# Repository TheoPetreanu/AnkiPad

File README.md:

# Theo’s Study Hackpad
This project was funded by a Blueprint (Hack Club) hardware grant, awarded following a design proposal and build journal review.

## Inspiration

I wanted to build a dedicated study-focused macropad to speed up my Anki revision and control YouTube without breaking focus. Instead of using keyboard shortcuts or mouse clicks, this hackpad allows for one handed control of my two most commonly used revision resources: Yotube and Anki.

## Challenges

One of the main challenges was designing a PCB that cleanly integrated mechanical switches, a rotary encoder, and addressable RGB LEDs while keeping the layout compact.

Another challenge was structuring the firmware cleanly using KMK, especially handling multiple modes (layers), encoder input, and an LED indicator

Designing the case to ensure proper alignment between the PCB, switches, encoder, and USB port also required several iterations.

## Specifications
### Modes:

Modes are switched by pressing the rotary encoder.

#### Anki Mode:

Blue LED indicator

Dedicated answer and control keys

#### YouTube Mode:

Red LED indicator

Playback and navigation controls

### BOM

1× XIAO RP2040

5× MX-style mechanical switches

5× Keycaps

1× EC11 Rotary encoder 

2× SK6812 MINI addressable RGB LEDs

Custom PCB

3D printed case (top + bottom)

USB Cable

### Firmware

KMK (CircuitPython-based firmware)

Two-layer setup (Anki / YouTube)

Encoder rotation for volume control

Encoder press for mode switching

RGB LEDs used as mode indicators

Firmware files are located in the firmware/ directory.

## Images
### Schematic

### PCB

### Case

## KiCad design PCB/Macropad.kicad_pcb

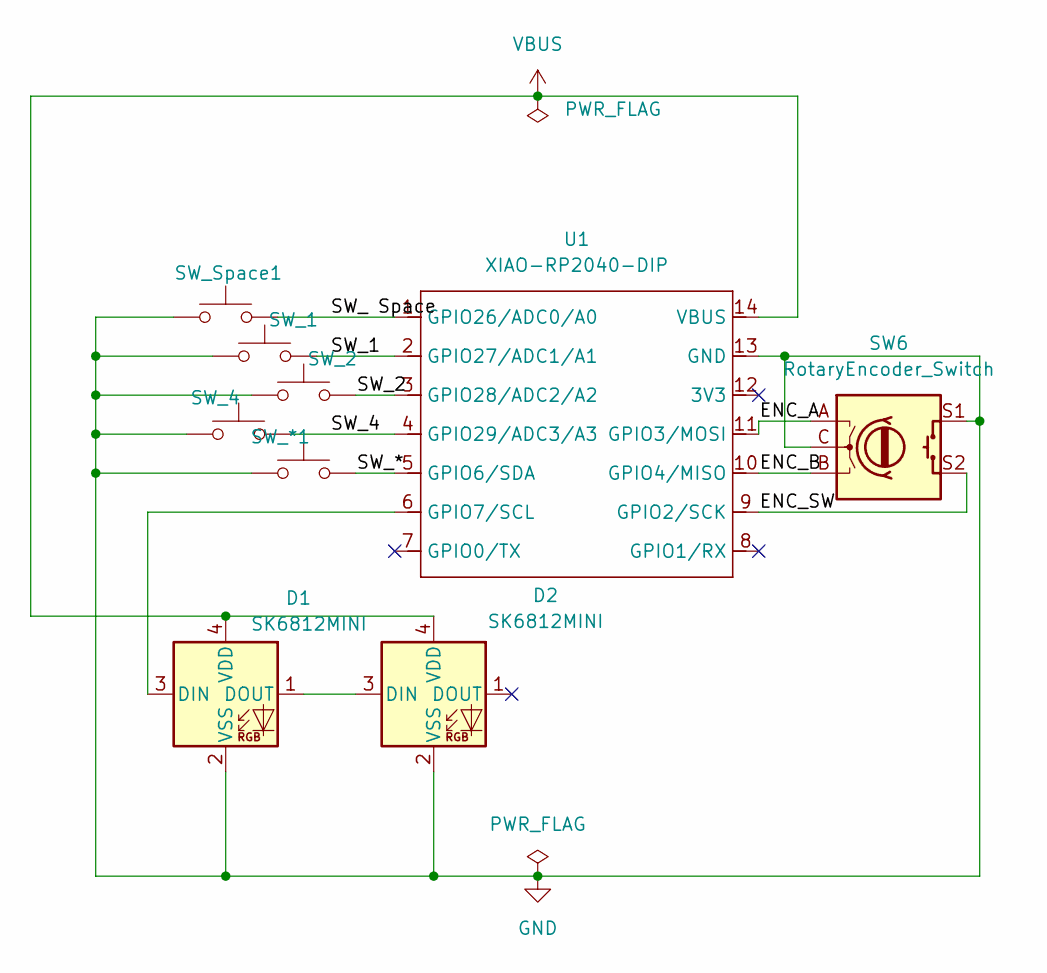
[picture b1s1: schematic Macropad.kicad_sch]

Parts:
D1, D2: SK6812MINI; LED_SK6812MINI_PLCC4_3.5x3.5mm_P1.75mm
SW6: RotaryEncoder_Switch; RotaryEncoder_Alps_EC11E-Switch_Vertical_H20mm
SW_1, SW_2, SW_4: SW_Push; SW_Cherry_MX_1.00u_PCB
SW_*1: SW_Push; SW_Cherry_MX_1.00u_PCB
SW_Space1: SW_Push; SW_Cherry_MX_1.00u_PCB
U1: XIAO-RP2040-DIP

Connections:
/ENC_A: SW6.A, U1.11 (GPIO3/MOSI)
/ENC_B: SW6.B, U1.10 (GPIO4/MISO)
/ENC_SW: SW6.S2, U1.9 (GPIO2/SCK)
/SW_1: SW_1.2, U1.2 (GPIO27/ADC1/A1)
/SW_2: SW_2.2, U1.3 (GPIO28/ADC2/A2)
/SW_4: SW_4.2, U1.4 (GPIO29/ADC3/A3)
/SW_ Space: SW_Space1.2, U1.1 (GPIO26/ADC0/A0)
/SW_*: SW_*1.2, U1.5 (GPIO6/SDA)
GND: D1.2 (VSS), D2.2 (VSS), SW6.C, SW6.S1, SW_1.1, SW_2.1, SW_4.1, SW_*1.1, SW_Space1.1, U1.13 (GND)
unnamed: D1.3 (DIN), U1.6 (GPIO7/SCL)
unnamed: D1.1 (DOUT), D2.3 (DIN)
VBUS: D1.4 (VDD), D2.4 (VDD), U1.14 (VBUS)

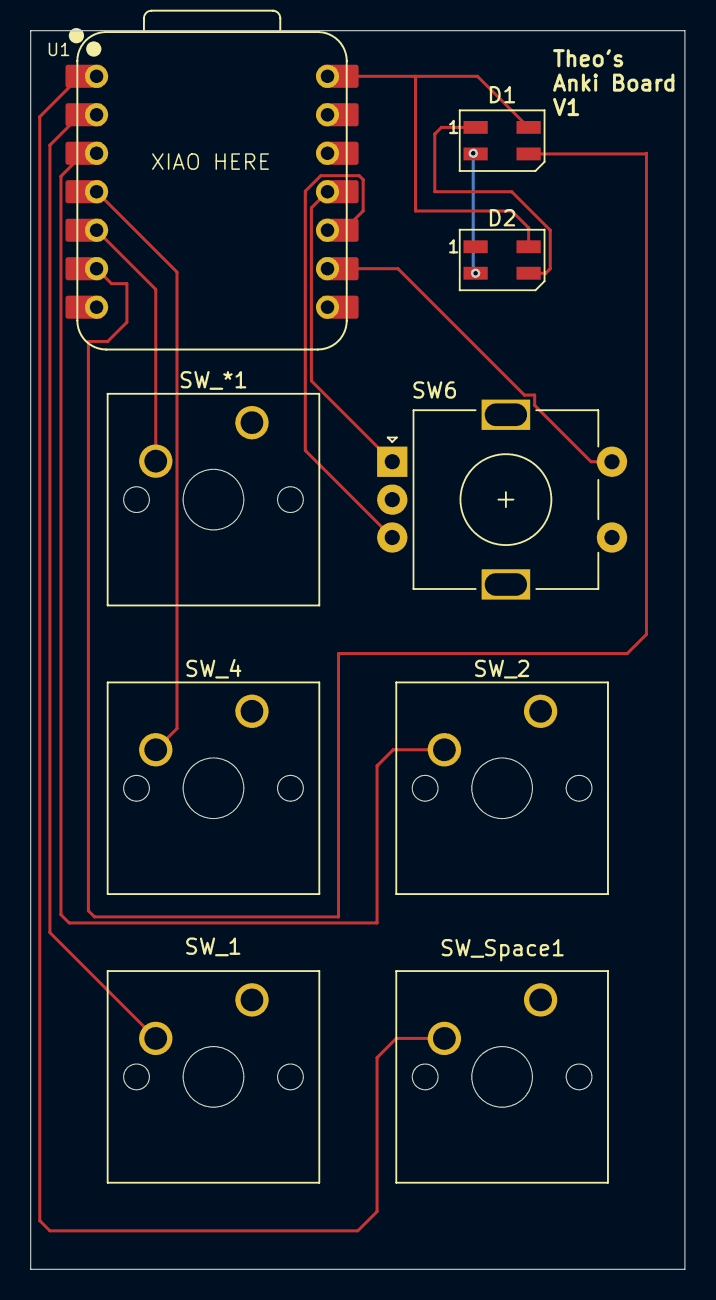
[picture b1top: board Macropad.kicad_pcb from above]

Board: 2 copper layers, 43.2 x 81.8 mm, 9 parts (0 on the bottom side), 12 nets.
